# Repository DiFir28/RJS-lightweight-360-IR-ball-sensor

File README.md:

# RJS-lightweight-360-IR-ball-sensor

## What is it for?

The RJS lightweight rules require the position of the ball emitting IR waves to be determined. 
>The ball's main emission period is 833 microseconds.

Learn more about [IR ball](https://github.com/robocup-junior/ir-golf-ball).
## Hardware solution
The sensor is a custom PCB. We use as main brain atmega2560. 24 TSSP4038 sensors are located around the circle to read the IR signal.

## Software solution

Due to the time limit of the ball study period and the need for uniform reading of the circle, at 833 microseconds, data is collected by bytes of pin registers and split into specific pins in a separate cycle. Vectors are constructed based on the sensors that receive the IR signal, with the beginning in the center of the board and the end in each sensor. We calculate a vector equal to the sum of all vectors constructed before the sensors, taking into account the vector on the sensor as many times as the IR signal was detected . The desired angle to the ball will be the angle of the final vector.
The sensor readings are transmitted via the I2C protocol.

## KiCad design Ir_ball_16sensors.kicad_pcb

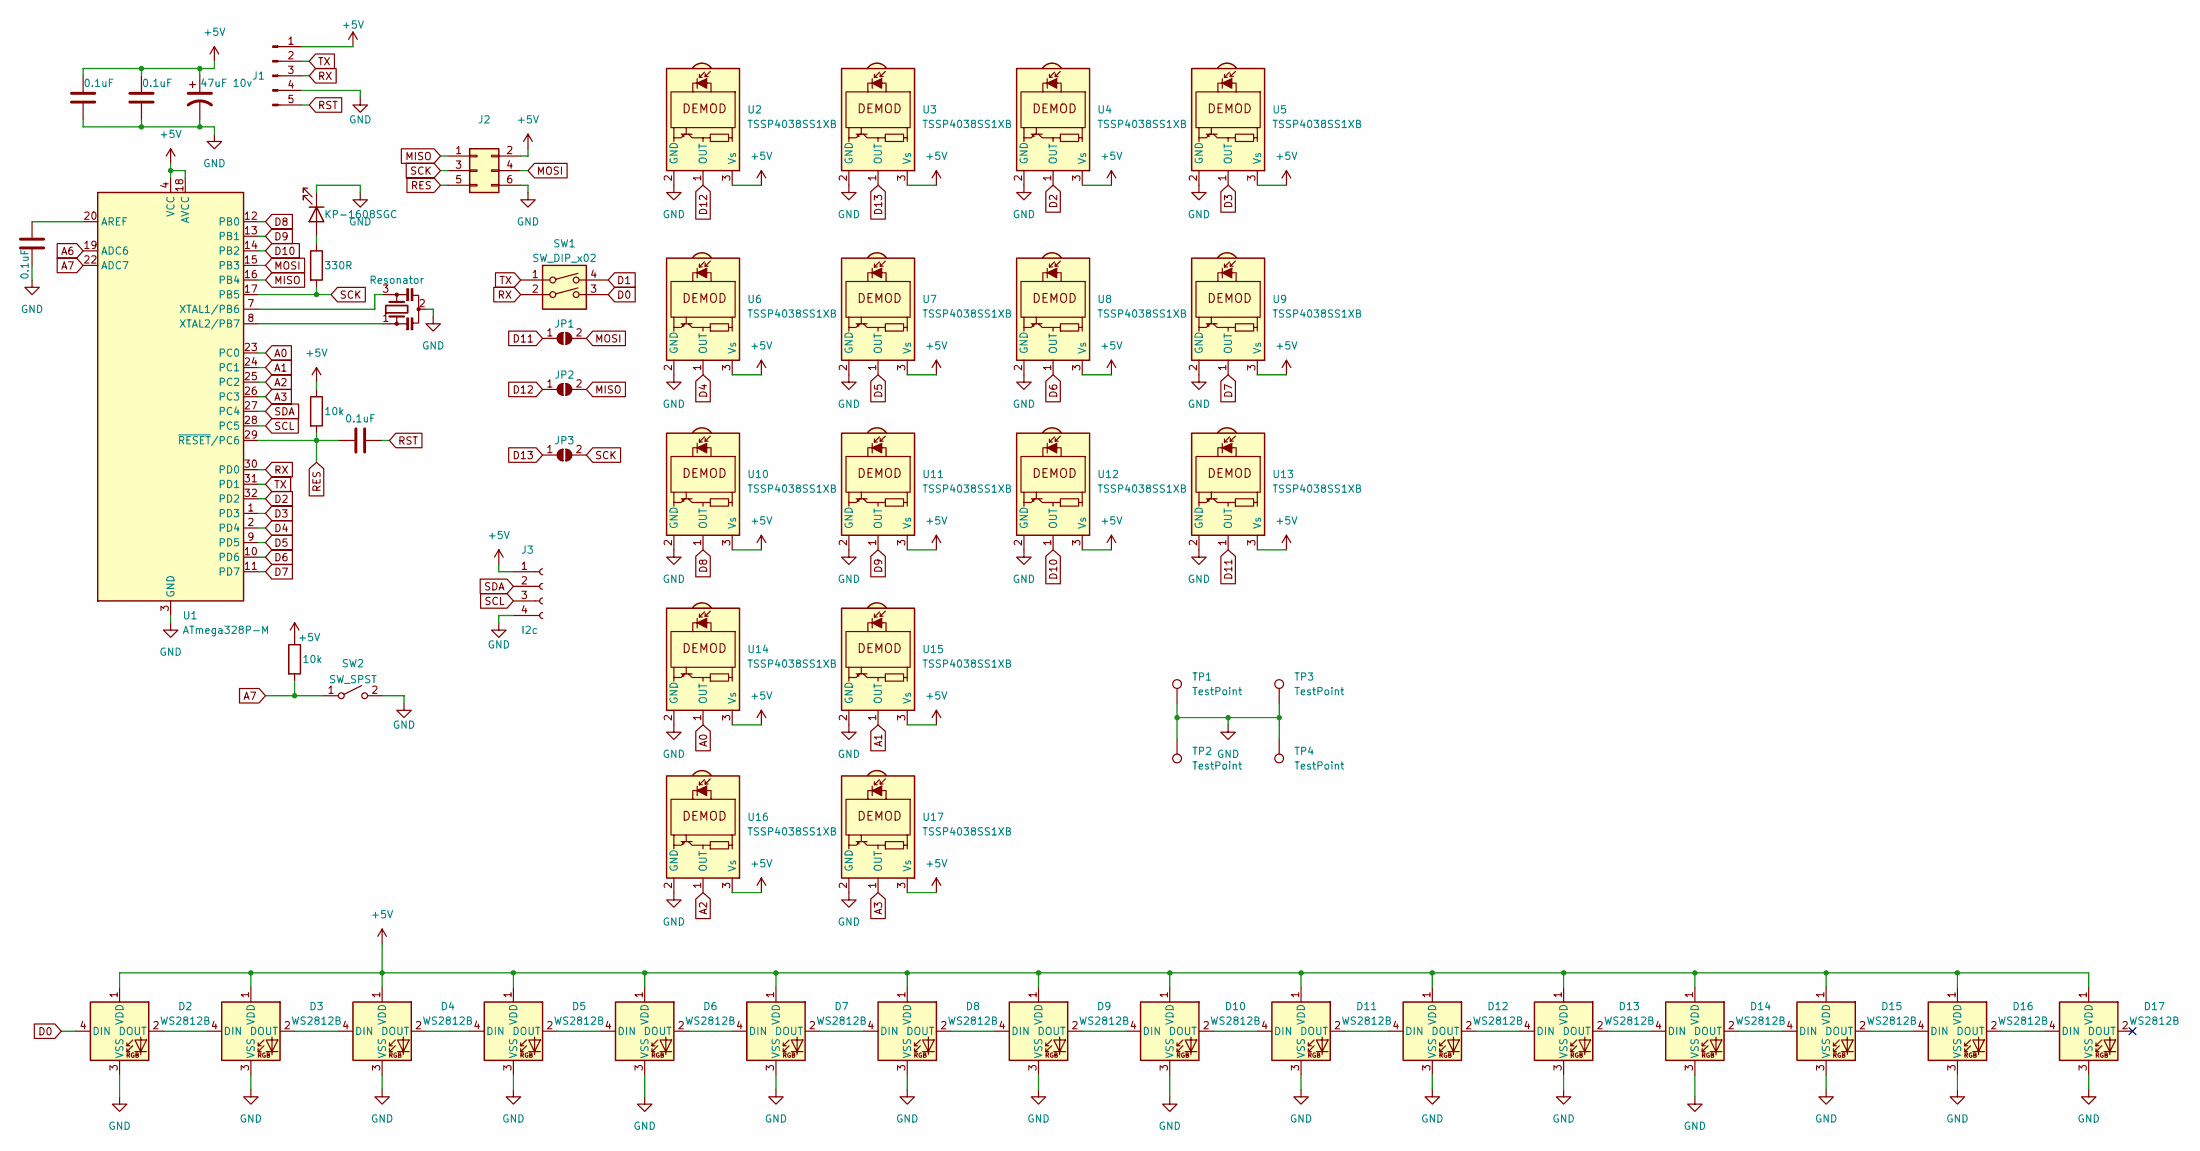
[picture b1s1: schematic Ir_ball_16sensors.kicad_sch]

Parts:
C1, C2, C4, C5: 0.1uF; C_0603_1608Metric_Pad1.08x0.95mm_HandSolder
C3: 47uF 10v; CP_EIA-3216-18_Kemet-A_Pad1.58x1.35mm_HandSolder
D1: KP-1608SGC; LED_0603_1608Metric_Pad1.05x0.95mm_HandSolder
D2, D3, D4, D5, D6, D7, D8, D9, D10, D11, D12, D13, D14, D15, D16, D17: WS2812B; WS2812
J1: Conn_01x05_Male; PinHeader_1x05_P2.54mm_Vertical
J2: Conn_02x03_Odd_Even; PinSocket_2x03_P2.54mm_Vertical
J3: I2c; PinHeader_1x04_P2.54mm_Vertical
JP1, JP2, JP3: SolderJumper_2_Open; SolderJumper-2_P1.3mm_Open_TrianglePad1.0x1.5mm
R1: 330R; R_0603_1608Metric_Pad0.98x0.95mm_HandSolder
R2, R3: 10k; R_0603_1608Metric_Pad0.98x0.95mm_HandSolder
SW1: SW_DIP_x02; SW_DIP_SPSTx02_Slide_KingTek_DSHP02TS_W7.62mm_P1.27mm
SW2: SW_SPST; SW_SPST_PTS645
TP1, TP2, TP3, TP4: TestPoint; TestPoint_Plated_Hole_D3.0mm
U1: ATmega328P-M; QFN-32-1EP_5x5mm_P0.5mm_EP3.1x3.1mm
U2, U3, U4, U5, U6, U7, U8, U9, U10, U11, U12, U13, U14, U15, U16, U17: TSSP4038SS1XB; Vishay_MINICAST-3Pin
Y1: Resonator; Resonator_SMD_Murata_CSTxExxV-3Pin_3.0x1.1mm_HandSoldering

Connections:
+5V: C1.2, C2.2, C3.1, D2.1 (VDD), D3.1 (VDD), D4.1 (VDD), D5.1 (VDD), D6.1 (VDD), D7.1 (VDD), D8.1 (VDD), D9.1 (VDD), D10.1 (VDD), D11.1 (VDD), D12.1 (VDD), D13.1 (VDD), D14.1 (VDD), D15.1 (VDD), D16.1 (VDD), D17.1 (VDD), J1.1, J2.2, J3.1, R2.1, R3.1, U1.4 (VCC), U1.6 (VCC), U1.18 (AVCC), U2.3 (Vs), U3.3 (Vs), U4.3 (Vs), U5.3 (Vs), U6.3 (Vs), U7.3 (Vs), U8.3 (Vs), U9.3 (Vs), U10.3 (Vs), U11.3 (Vs), U12.3 (Vs), U13.3 (Vs), U14.3 (Vs), U15.3 (Vs), U16.3 (Vs), U17.3 (Vs)
A0: U1.23 (PC0), U14.1 (OUT)
A1: U1.24 (PC1), U15.1 (OUT)
A2: U1.25 (PC2), U16.1 (OUT)
A3: U1.26 (PC3), U17.1 (OUT)
A6: U1.19 (ADC6)
A7: R3.2, SW2.1 (A), U1.22 (ADC7)
D0: D2.4 (DIN), SW1.3
D1: SW1.4
D2: U1.32 (PD2), U4.1 (OUT)
D3: U1.1 (PD3), U5.1 (OUT)
D4: U1.2 (PD4), U6.1 (OUT)
D5: U1.9 (PD5), U7.1 (OUT)
D6: U1.10 (PD6), U8.1 (OUT)
D7: U1.11 (PD7), U9.1 (OUT)
D8: U1.12 (PB0), U10.1 (OUT)
D9: U1.13 (PB1), U11.1 (OUT)
D10: U1.14 (PB2), U12.1 (OUT)
D11: JP1.1 (A), U13.1 (OUT)
D12: JP2.1 (A), U2.1 (OUT)
D13: JP3.1 (A), U3.1 (OUT)
GND: C1.1, C2.1, C3.2, C5.1, D1.1 (K), D2.3 (VSS), D3.3 (VSS), D4.3 (VSS), D5.3 (VSS), D6.3 (VSS), D7.3 (VSS), D8.3 (VSS), D9.3 (VSS), D10.3 (VSS), D11.3 (VSS), D12.3 (VSS), D13.3 (VSS), D14.3 (VSS), D15.3 (VSS), D16.3 (VSS), D17.3 (VSS), J1.4, J2.6, J3.4, SW2.2 (B), TP1.1, TP2.1, TP3.1, TP4.1, U1.3 (GND), U1.5 (GND), U1.21 (GND), U1.33 (GND), U2.2 (GND), U3.2 (GND), U4.2 (GND), U5.2 (GND), U6.2 (GND), U7.2 (GND), U8.2 (GND), U9.2 (GND), U10.2 (GND), U11.2 (GND), U12.2 (GND), U13.2 (GND), U14.2 (GND), U15.2 (GND), U16.2 (GND), U17.2 (GND), Y1.2
MISO: J2.1, JP2.2 (B), U1.16 (PB4)
MOSI: J2.4, JP1.2 (B), U1.15 (PB3)
unnamed: C5.2, U1.20 (AREF)
unnamed: D1.2 (A), R1.1
unnamed: D2.2 (DOUT), D3.4 (DIN)
unnamed: D3.2 (DOUT), D4.4 (DIN)
unnamed: D4.2 (DOUT), D5.4 (DIN)
unnamed: D5.2 (DOUT), D6.4 (DIN)
unnamed: D6.2 (DOUT), D7.4 (DIN)
unnamed: D7.2 (DOUT), D8.4 (DIN)
unnamed: D8.2 (DOUT), D9.4 (DIN)
unnamed: D10.2 (DOUT), D11.4 (DIN)
unnamed: D9.2 (DOUT), D10.4 (DIN)
unnamed: D11.2 (DOUT), D12.4 (DIN)
unnamed: D12.2 (DOUT), D13.4 (DIN)
unnamed: D13.2 (DOUT), D14.4 (DIN)
unnamed: D14.2 (DOUT), D15.4 (DIN)
unnamed: D15.2 (DOUT), D16.4 (DIN)
unnamed: D16.2 (DOUT), D17.4 (DIN)
unnamed: U1.7 (XTAL1/PB6), Y1.3
unnamed: U1.8 (XTAL2/PB7), Y1.1
RES: C4.1, J2.5, R2.2, U1.29 (~RESET/PC6)
RST: C4.2, J1.5
RX: J1.3, SW1.2, U1.30 (PD0)
SCK: J2.3, JP3.2 (B), R1.2, U1.17 (PB5)
SCL: J3.3, U1.28 (PC5)
SDA: J3.2, U1.27 (PC4)
TX: J1.2, SW1.1, U1.31 (PD1)

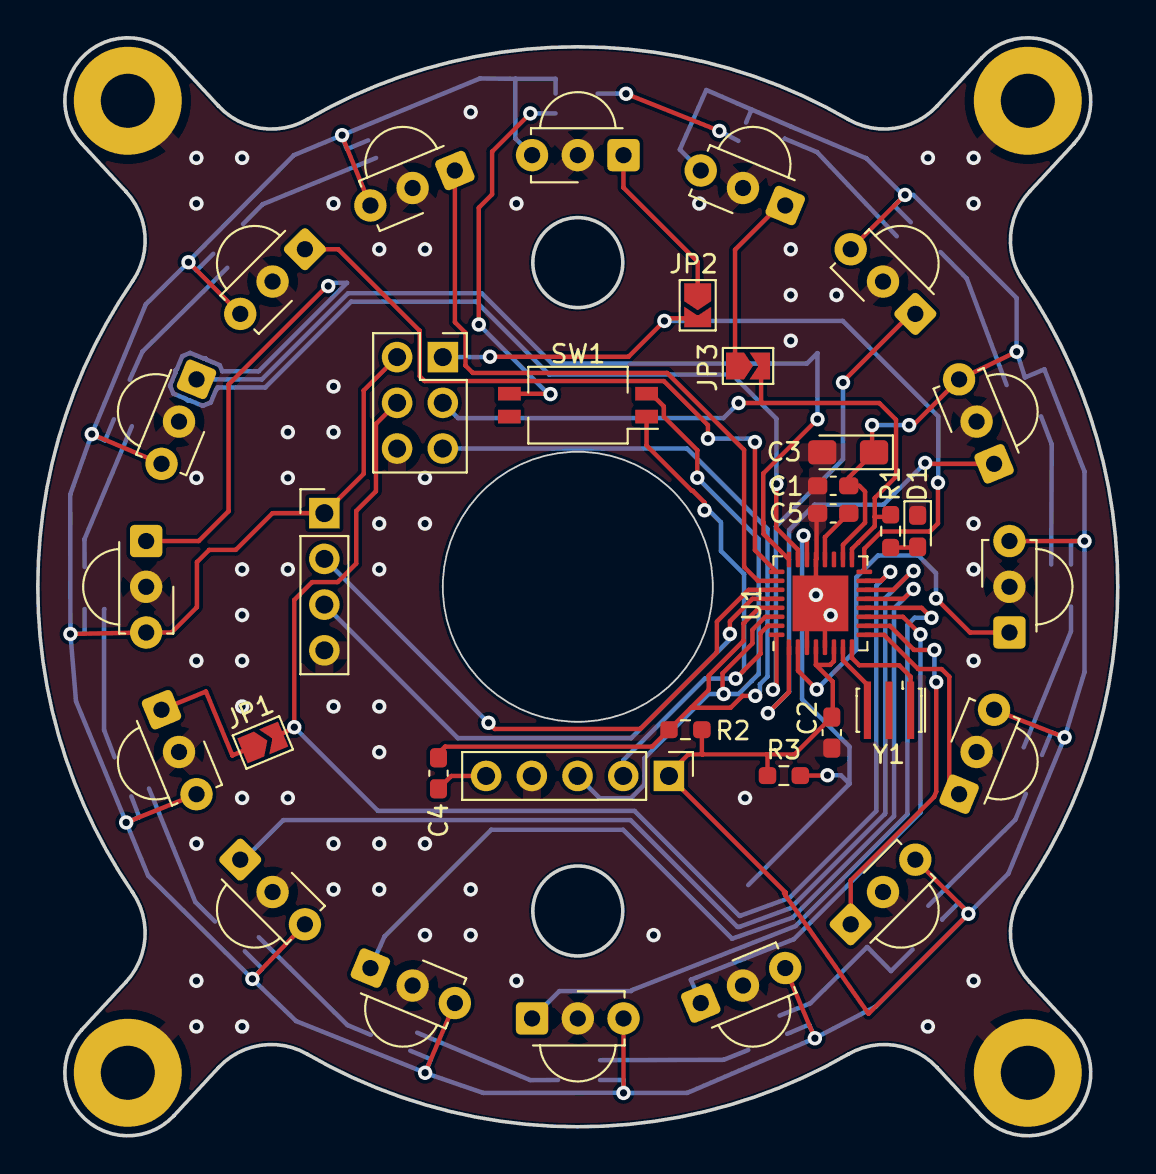
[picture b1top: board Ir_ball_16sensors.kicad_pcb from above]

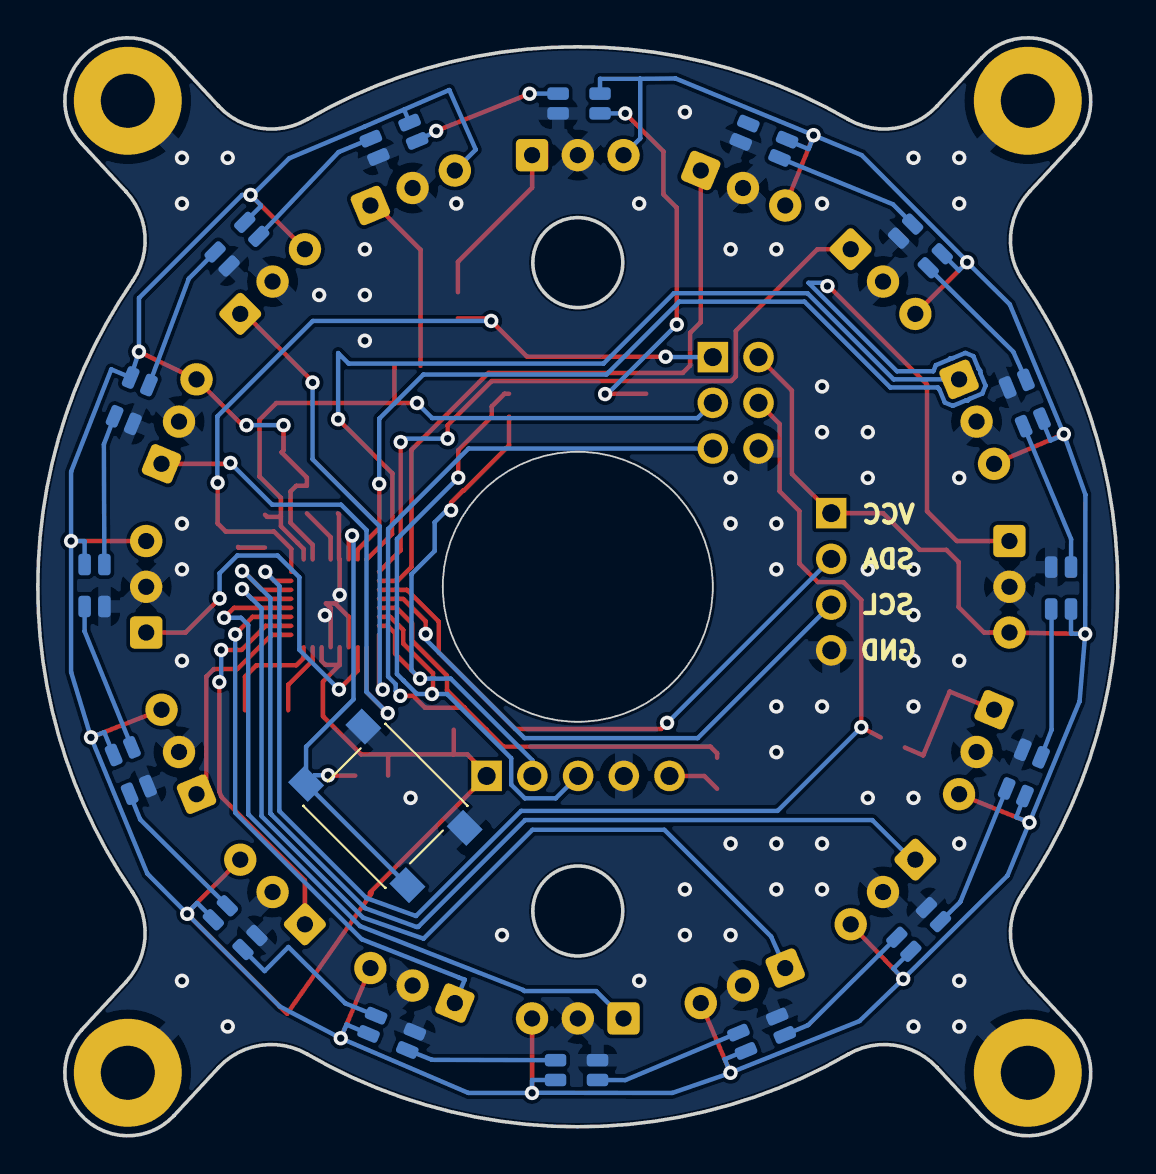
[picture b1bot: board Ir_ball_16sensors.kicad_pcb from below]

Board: 2 copper layers, 60.0 x 61.0 mm, 55 parts (17 on the bottom side), 48 nets.

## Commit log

2025-10-01 Upload code
2025-10-01 Update README.md
    Update readme
2025-11-28 16_sensors_update
2025-11-28 Update struct of repository
2025-11-29 Add pcb
